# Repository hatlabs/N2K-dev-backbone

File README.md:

# NMEA 2000 development backbone

I needed a simple way to connect different NMEA 2000 compliant CAN bus devices together for development and testing purposes and put together this simple hub or development backbone. To provide shielding to the cables, cable shields should be connected to GND at the connectors.

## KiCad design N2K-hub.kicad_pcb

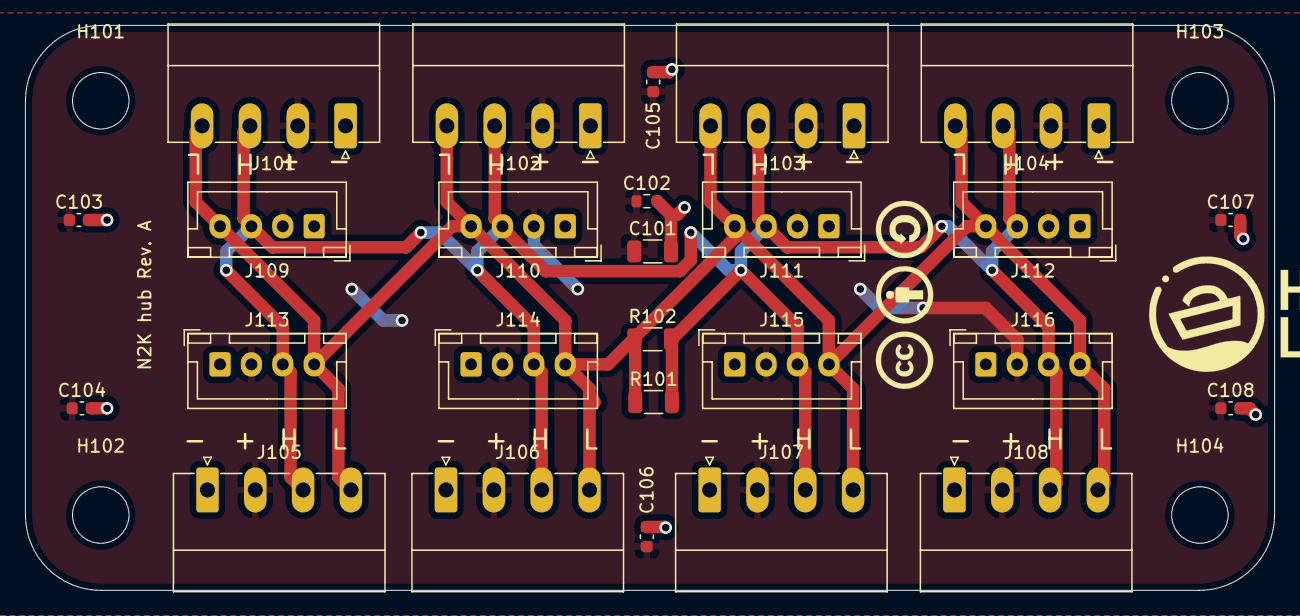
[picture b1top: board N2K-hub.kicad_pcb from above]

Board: 2 copper layers, 99.5 x 45.0 mm, 30 parts (0 on the bottom side), 4 nets.

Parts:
C101: 10uF; R_1206_3216Metric
C102: 100nF; R_0603_1608Metric
C103, C104, C105, C106, C107, C108: 100n; C_0603_1608Metric
H101, H102, H103, H104: MountingHole; MountingHole_4.5mm
J101, J102, J103, J104, J105, J106, J107, J108: Conn_01x04; PhoenixContact_MC_1,5_4-G-3.81_1x04_P3.81mm_Horizontal
J109, J110, J111, J112, J113, J114, J115, J116: Conn_01x04; JST_XH_B4B-XH-A_1x04_P2.50mm_Vertical
R101, R102: 120R; R_1206_3216Metric

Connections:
/CANH: J101.3, J102.3, J103.3, J104.3, J105.3, J106.3, J107.3, J108.3, J109.3, J110.3, J111.3, J112.3, J113.3, J114.3, J115.3, J116.3, R101.2, R102.2
/CANL: J101.4, J102.4, J103.4, J104.4, J105.4, J106.4, J107.4, J108.4, J109.4, J110.4, J111.4, J112.4, J113.4, J114.4, J115.4, J116.4, R101.1, R102.1
/VCC: C101.1, C102.1, C103.1, C104.1, C105.1, C106.1, C107.1, C108.1, J101.2, J102.2, J103.2, J104.2, J105.2, J106.2, J107.2, J108.2, J109.2, J110.2, J111.2, J112.2, J113.2, J114.2, J115.2, J116.2
GND: C101.2, C102.2, C103.2, C104.2, C105.2, C106.2, C107.2, C108.2, J101.1, J102.1, J103.1, J104.1, J105.1, J106.1, J107.1, J108.1, J109.1, J110.1, J111.1, J112.1, J113.1, J114.1, J115.1, J116.1

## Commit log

2021-02-14 initial import
2021-02-14 Add a license and a README file
2021-02-14 Add footprint library
2021-02-14 Rename project to N2K-dev-backbone
2021-02-14 Add .gitignore
